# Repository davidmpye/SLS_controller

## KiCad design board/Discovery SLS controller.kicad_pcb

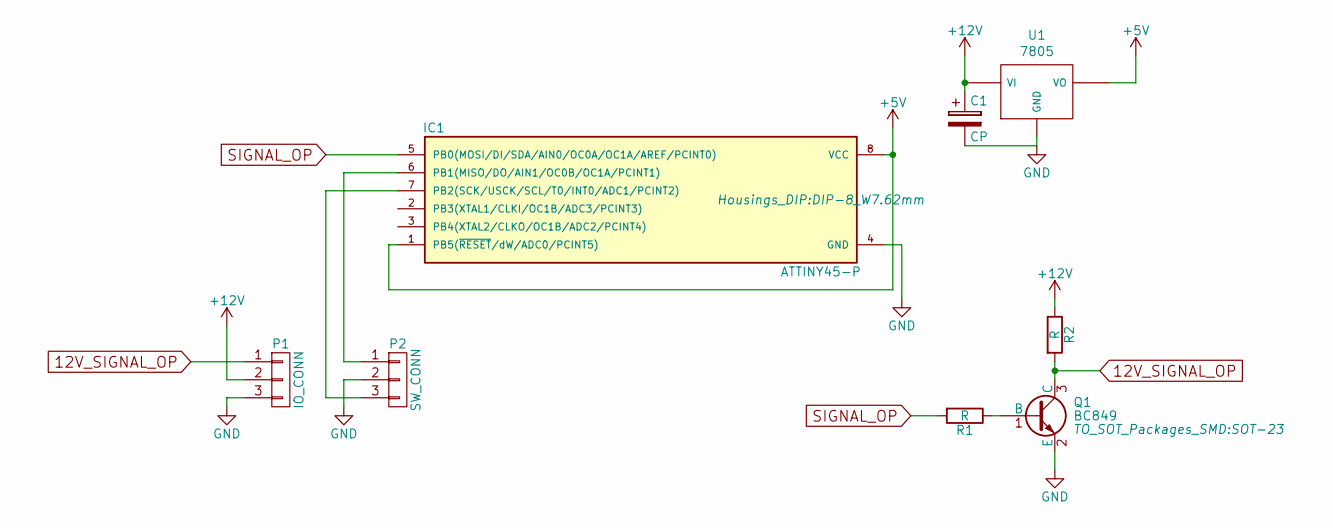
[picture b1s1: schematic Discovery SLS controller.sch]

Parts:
C1: CP; TantalC_SizeA_EIA-3216_HandSoldering
IC1: ATTINY45-P; DIP-8_W7.62mm
P1: IO_CONN; Pin_Header_Straight_1x03
P2: SW_CONN; Pin_Header_Straight_1x03
Q1: BC849; SOT-23
R1, R2: R; R_0805_HandSoldering
U1: 7805; TO-92_Molded_Narrow

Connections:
12V_SIGNAL_OP: P1.1, Q1.3 (C), R2.2
+5V: IC1.1 (PB5(~RESET~/dW/ADC0/PCINT5)), IC1.8 (VCC), U1.1 (VO)
+12V: C1.1, P1.2, R2.1, U1.3 (VI)
GND: C1.2, IC1.4 (GND), P1.3, P2.2, Q1.2 (E), U1.2 (GND)
unnamed: IC1.6 (PB1(MISO/DO/AIN1/OC0B/OC1A/PCINT1)), P2.1
unnamed: IC1.7 (PB2(SCK/USCK/SCL/T0/INT0/ADC1/PCINT2)), P2.3
unnamed: Q1.1 (B), R1.1
SIGNAL_OP: IC1.5 (PB0(MOSI/DI/SDA/AIN0/OC0A/OC1A/AREF/PCI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), R1.2

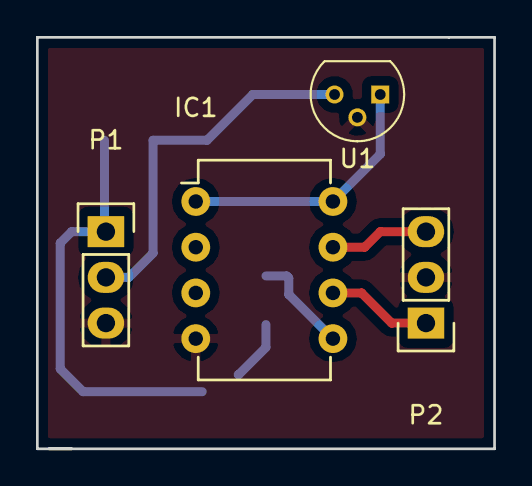
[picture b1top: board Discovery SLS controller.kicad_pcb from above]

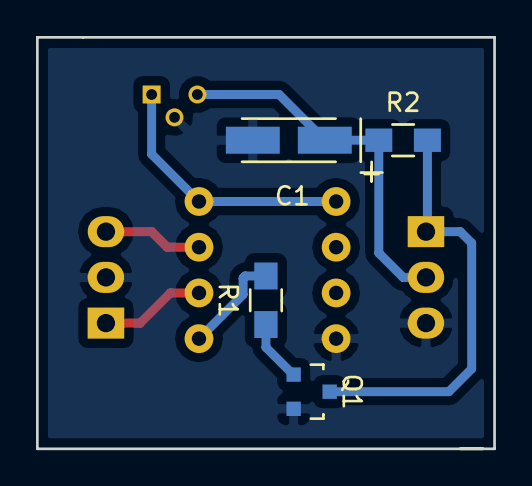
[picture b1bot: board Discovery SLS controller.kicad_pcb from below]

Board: 2 copper layers, 25.4 x 22.9 mm, 8 parts (4 on the bottom side), 8 nets.

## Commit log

2016-10-12 Initial import
2016-10-12 Board initial import
2016-10-12 Update to 1.3 v board (untested)
2017-07-29 Change project to KiCAD
2017-07-29 Add gerbers
2017-08-02 Update to make 3d view display properly
